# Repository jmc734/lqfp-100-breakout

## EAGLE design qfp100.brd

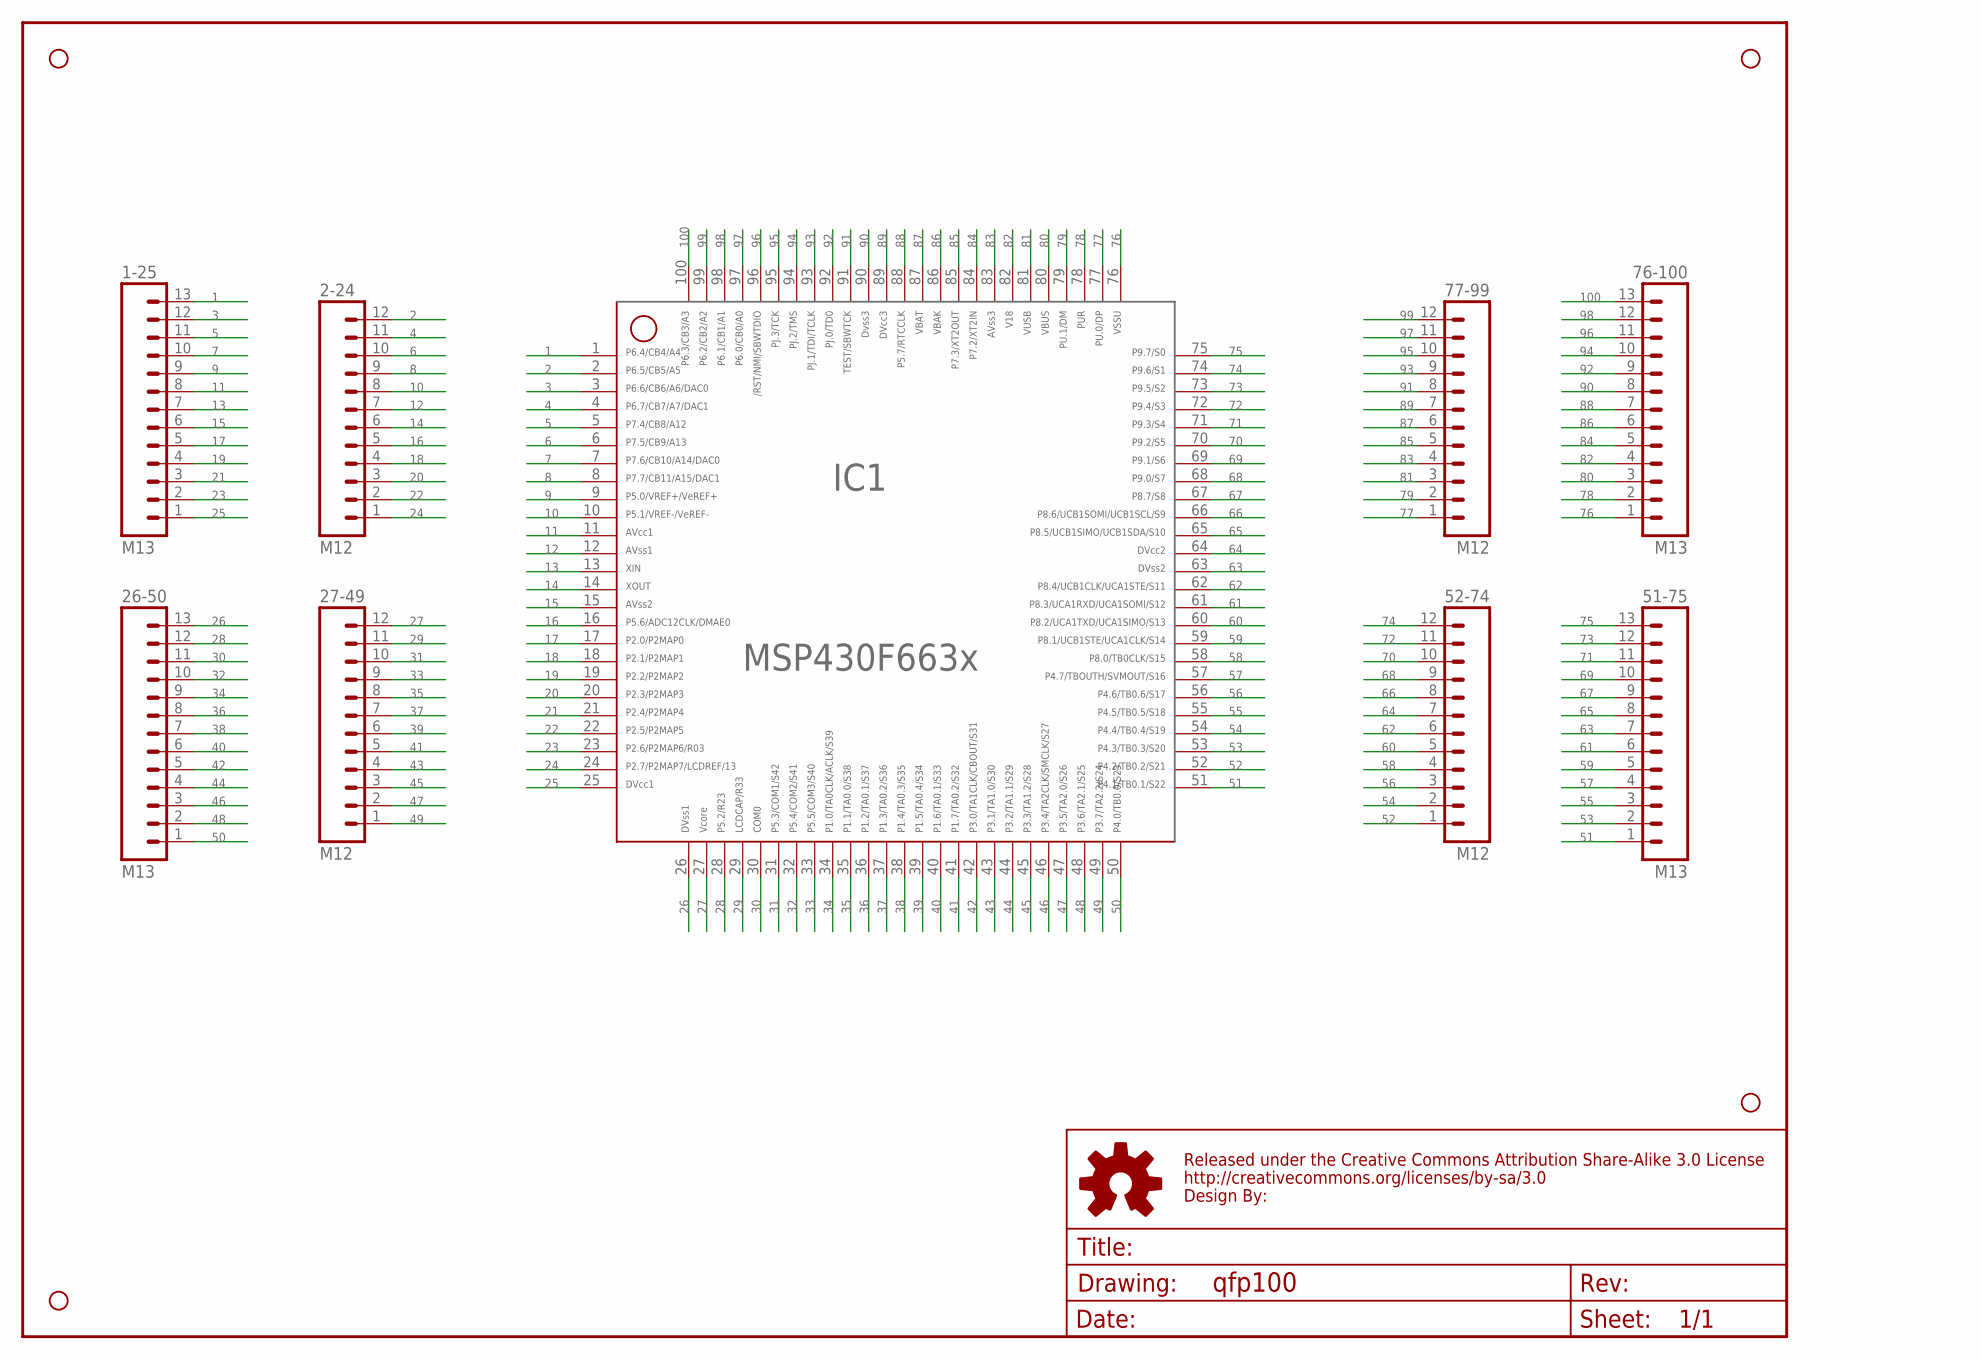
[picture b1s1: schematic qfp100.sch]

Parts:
1-25, 26-50, 51-75, 76-100: M13; 1X13
2-24, 27-49, 52-74, 77-99: M12; 1X12
FRAME1: FRAME-LETTER; CREATIVE_COMMONS
IC1: F66XX---PZ100EXTENDED; PZ100-EXTENDED
JP1, JP2, JP3, JP4: STAND-OFF

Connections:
1: 1-25.13, IC1.1
2: 2-24.12, IC1.2
3: 1-25.12, IC1.3
4: 2-24.11, IC1.4
5: 1-25.11, IC1.5
6: 2-24.10, IC1.6
7: 1-25.10, IC1.7
8: 2-24.9, IC1.8
9: 1-25.9, IC1.9
10: 2-24.8, IC1.10
11: 1-25.8, IC1.11
12: 2-24.7, IC1.12
13: 1-25.7, IC1.13
14: 2-24.6, IC1.14
15: 1-25.6, IC1.15
16: 2-24.5, IC1.16
17: 1-25.5, IC1.17
18: 2-24.4, IC1.18
19: 1-25.4, IC1.19
20: 2-24.3, IC1.20
21: 1-25.3, IC1.21
22: 2-24.2, IC1.22
23: 1-25.2, IC1.23
24: 2-24.1, IC1.24
25: 1-25.1, IC1.25
26: 26-50.13, IC1.26
27: 27-49.12, IC1.27
28: 26-50.12, IC1.28
29: 27-49.11, IC1.29
30: 26-50.11, IC1.30
31: 27-49.10, IC1.31
32: 26-50.10, IC1.32
33: 27-49.9, IC1.33
34: 26-50.9, IC1.34
35: 27-49.8, IC1.35
36: 26-50.8, IC1.36
37: 27-49.7, IC1.37
38: 26-50.7, IC1.38
39: 27-49.6, IC1.39
40: 26-50.6, IC1.40
41: 27-49.5, IC1.41
42: 26-50.5, IC1.42
43: 27-49.4, IC1.43
44: 26-50.4, IC1.44
45: 27-49.3, IC1.45
46: 26-50.3, IC1.46
47: 27-49.2, IC1.47
48: 26-50.2, IC1.48
49: 27-49.1, IC1.49
50: 26-50.1, IC1.50
51: 51-75.1, IC1.51
52: 52-74.1, IC1.52
53: 51-75.2, IC1.53
54: 52-74.2, IC1.54
55: 51-75.3, IC1.55
56: 52-74.3, IC1.56
57: 51-75.4, IC1.57
58: 52-74.4, IC1.58
59: 51-75.5, IC1.59
60: 52-74.5, IC1.60
61: 51-75.6, IC1.61
62: 52-74.6, IC1.62
63: 51-75.7, IC1.63
64: 52-74.7, IC1.64
65: 51-75.8, IC1.65
66: 52-74.8, IC1.66
67: 51-75.9, IC1.67
68: 52-74.9, IC1.68
69: 51-75.10, IC1.69
70: 52-74.10, IC1.70
71: 51-75.11, IC1.71
72: 52-74.11, IC1.72
73: 51-75.12, IC1.73
74: 52-74.12, IC1.74
75: 51-75.13, IC1.75
76: 76-100.1, IC1.76
77: 77-99.1, IC1.77
78: 76-100.2, IC1.78
79: 77-99.2, IC1.79
80: 76-100.3, IC1.80
81: 77-99.3, IC1.81
82: 76-100.4, IC1.82
83: 77-99.4, IC1.83
84: 76-100.5, IC1.84
85: 77-99.5, IC1.85
86: 76-100.6, IC1.86
87: 77-99.6, IC1.87
88: 76-100.7, IC1.88
89: 77-99.7, IC1.89
90: 76-100.8, IC1.90
91: 77-99.8, IC1.91
92: 76-100.9, IC1.92
93: 77-99.9, IC1.93
94: 76-100.10, IC1.94
95: 77-99.10, IC1.95
96: 76-100.11, IC1.96
97: 77-99.11, IC1.97
98: 76-100.12, IC1.98
99: 77-99.12, IC1.99
100: 76-100.13, IC1.100

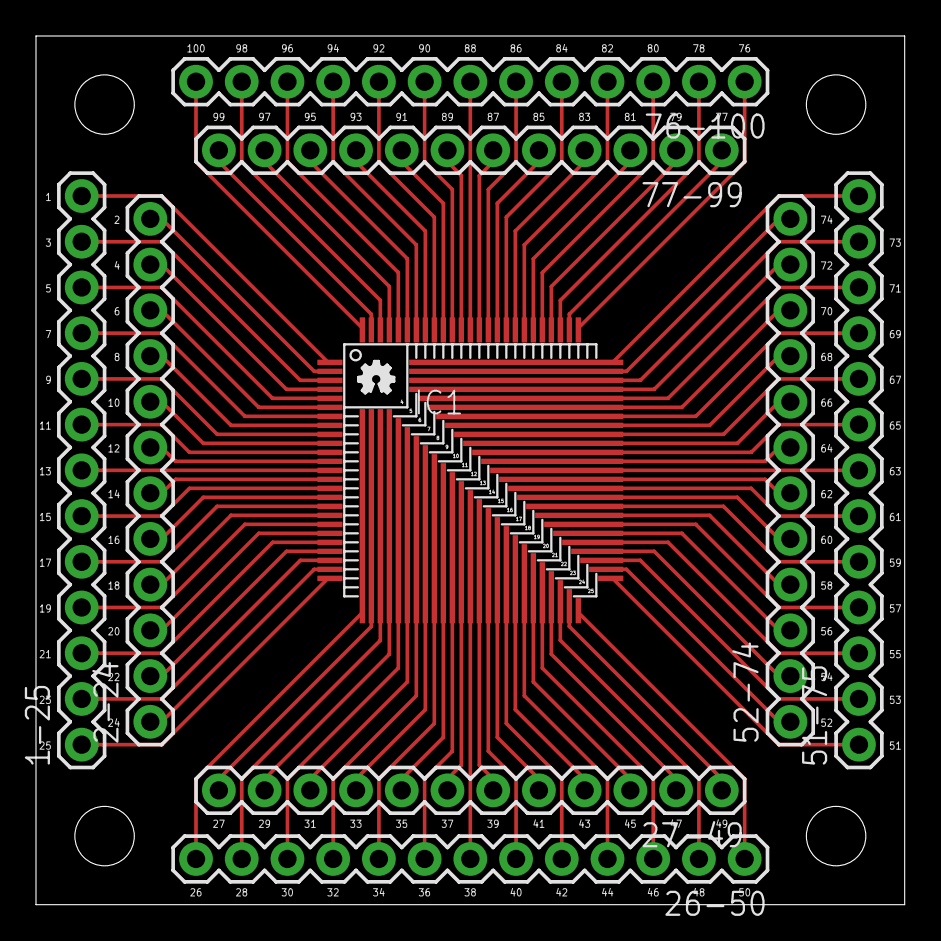
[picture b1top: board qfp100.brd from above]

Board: 2 copper layers, 48.3 x 48.3 mm, 15 parts (0 on the bottom side), 100 nets.

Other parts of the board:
U$1: OSHW-LOGO-XS

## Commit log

2013-08-04 First revision of the breakout board
2013-08-04 Shrunk board to fit within the 5cmx5cm form factor that allows for very cheap manufacture from services like Seeed Fusion
2013-08-04 Changed the revision number to 1.0
2013-08-04 Changed revision number to 1
2013-08-04 Added images of board and schematic

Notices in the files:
parts and their libraries:
SparkFun: Licensing: CC v3.0 Share-Alike You are welcome to use this library for commercial purposes.
SparkFun-Aesthetics: Released under the Creative Commons Attribution Share-Alike 3.0 License
SparkFun-Aesthetics: http://creativecommons.org/licenses/by-sa/3.0
